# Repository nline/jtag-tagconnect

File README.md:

JTAG to Tag Connect
===================

This PCB is an adapter that converts the [20 pin JLink](https://www.segger.com/jlink-debug-probes.html) connector to
a [6-pin Tag Connect](http://www.tag-connect.com/TC2030-IDC-NL),
much like [this](https://www.segger.com/jlink-6-pin-adapter.html) board.
Ours, however, additionally contains an onboard LDO
that can supply 3.3V to the attached device and the VTRef pin on the J-Link programmer
so that it can program boards that are not self powered.

This most recent (nLine) version allows you to additionally power the target board with 5V and
also select the whether to keep the I/O at the supply voltage or divide it down from 5V to 3V3. 
This allows powering higher voltage boards while still operating the MCU at 3V3 without on-board
level shifters.

Interface
---------

- **Switch 1**, labeled `VSupply`: Set to 5V to connect teh VCC pin on the TagConnect
header (and the attached board) to the 5VC output from the JLink.
Set to `3V3` to connect the `VCC` pin on the TagConnect
header (and the attached board to be programmed) and the `VTRef` pin from
the Segger JLink to the 3.3 V output from the regulator.
Set to `DEV` to directly connect the `VTRef` pin on the JLink to the TagConnect
VCC pin. This sets the I/O voltage for the JLink, but does not power the target board.

- **Switch 2**, labeled `SWDIO`: This switch can connect the `SWDIO` and
`!RESET` signals, which is needed on some ICs. To leave the signals
disconnected, leave the switch in the empty (down) position.

- **Switch 3** labeled `VIO`: Set to `Supply` to use with I/O voltage same as VSupply. Set to
`5V->3V3` to divide a 5V supply down to 3V3 for 3V3 I/O operation.

Troubleshooting
---------------

1. Blue LED does not come on when attached to JLink.
You need to enable the 5 V output on the JLink:

        $ JlinkExe
        power on perm

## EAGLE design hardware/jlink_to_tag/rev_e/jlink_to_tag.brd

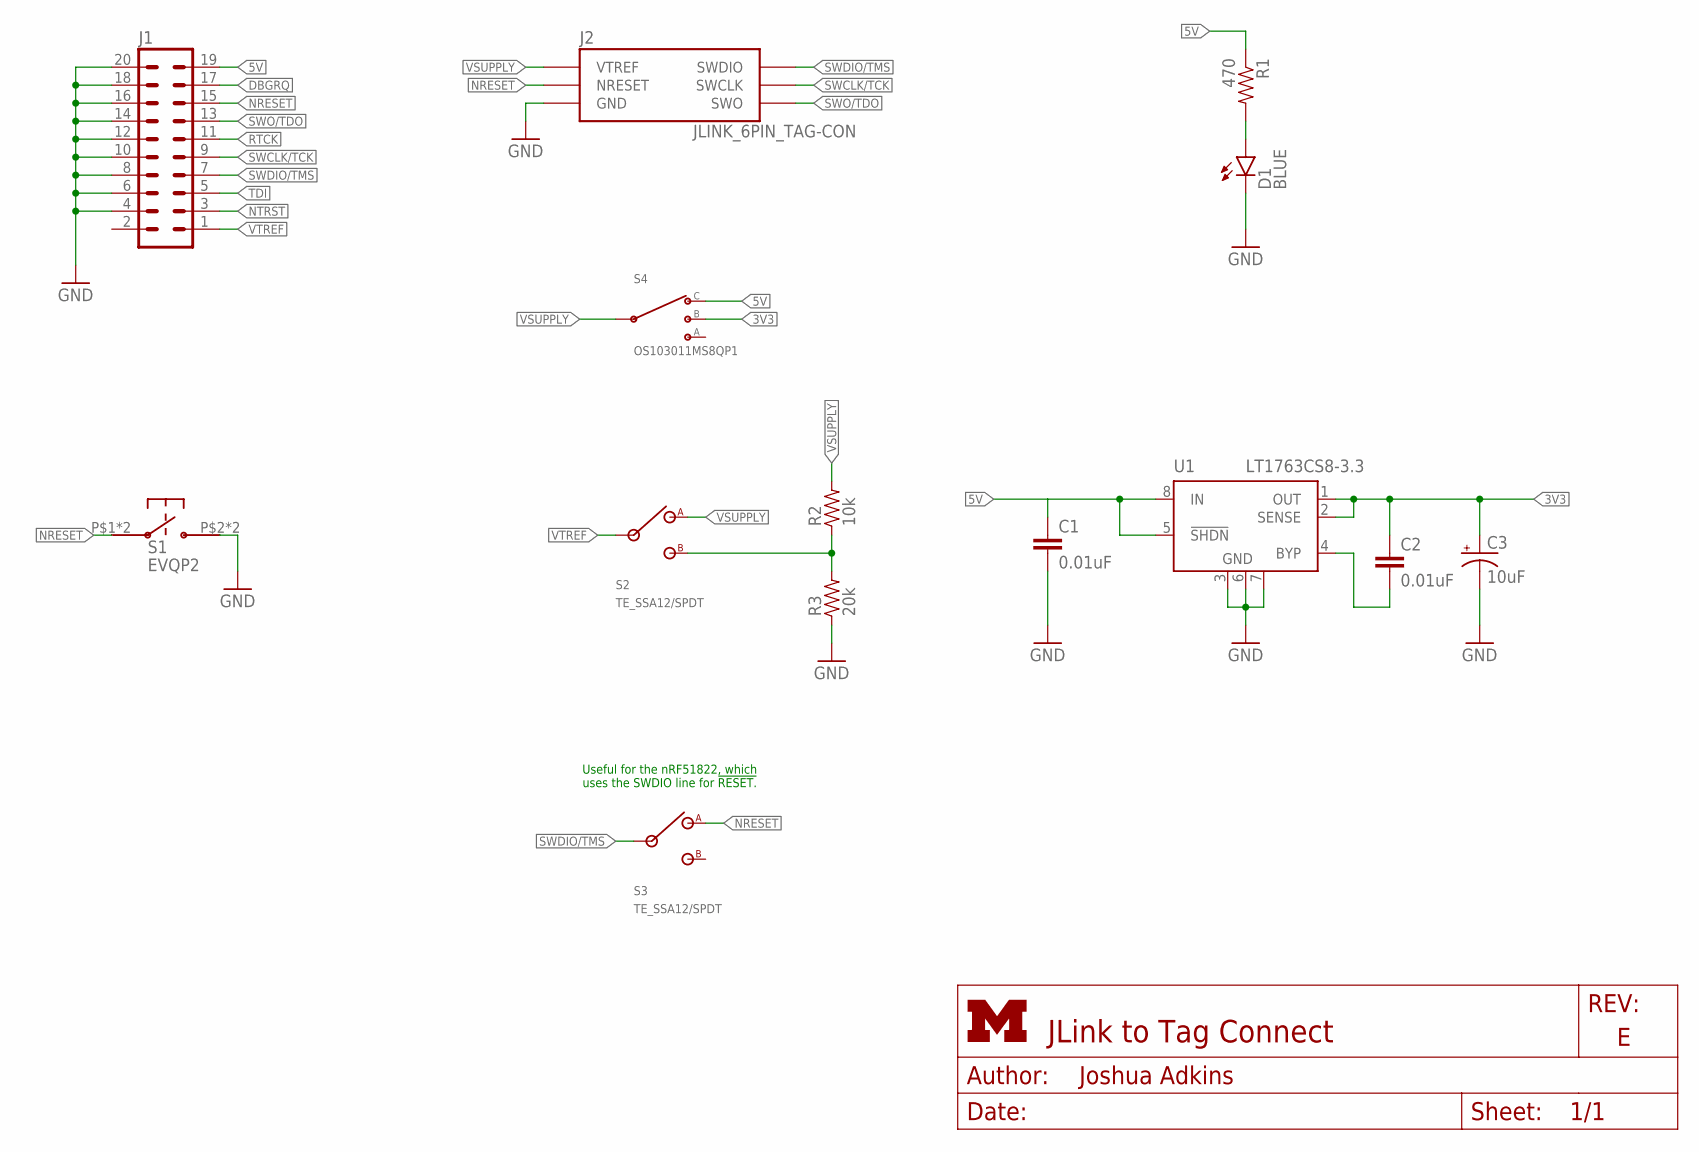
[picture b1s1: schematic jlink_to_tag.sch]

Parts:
C1, C2: 0.01uF; C0603; DIGIKEY 490-1512-1-ND
C3: 10uF; EIA3216; DIGIKEY 399-3684-1-ND
D1: BLUE; LED-0603; DIGIKEY 160-1827-1-ND
J1: ML20; DIGIKEY S9172-ND
J2: JLINK_6PIN_TAG-CON; 2X3_MALE_SHROUDED_0.100
R1: 470; 0603-RES; DIGIKEY P470DBCT-ND
R2: 10k; 0603-RES; DIGIKEY RMCF0603FT10K0CT-ND
R3: 20k; 0603-RES; DIGIKEY P20.0KHCT-ND
S1: EVQP2
S2, S3: TE_SSA12/SPDT; MPN SLW-883935-2A-D; DIGIKEY 2223-SLW-883935-2A-D-ND
S4: OS103011MS8QP1; OS102011MS8QP1
U1: LT1763CS8-3.3; SOIC8; DIGIKEY LT1763CS8-3.3#TRPBFCT-ND

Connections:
3V3: C2.1, C3.A (+), S4.3 (2), U1.1 (OUT), U1.2 (SENSE)
5V: C1.1, J1.19, R1.1, S4.4 (3), U1.5 (!SHDN), U1.8 (IN)
DBGRQ: J1.17
GND: C1.2, C3.C (-), D1.C, J1.4, J1.6, J1.8, J1.10, J1.12, J1.14, J1.16, J1.18, J1.20, J2.5 (GND), R3.1, S1.P$2, S1.P$4, U1.3 (GND), U1.6 (GND), U1.7 (GND)
unnamed: R2.1, R3.2, S2.2 (B)
unnamed: D1.A, R1.2
unnamed: C2.2, U1.4 (BYP)
NRESET: J1.15, J2.3 (NRESET), S1.P$1, S1.P$3, S3.1 (A)
NTRST: J1.3
RTCK: J1.11
SWCLK/TCK: J1.9, J2.4 (SWCLK)
SWDIO/TMS: J1.7, J2.2 (SWDIO), S3.IN
SWO/TDO: J1.13, J2.6 (SWO)
TDI: J1.5
VSUPPLY: J2.1 (VTREF), R2.2, S2.1 (A), S4.2 (C)
VTREF: J1.1, S2.IN

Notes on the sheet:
Useful for the nRF51822, which uses the SWDIO line for !RESET.

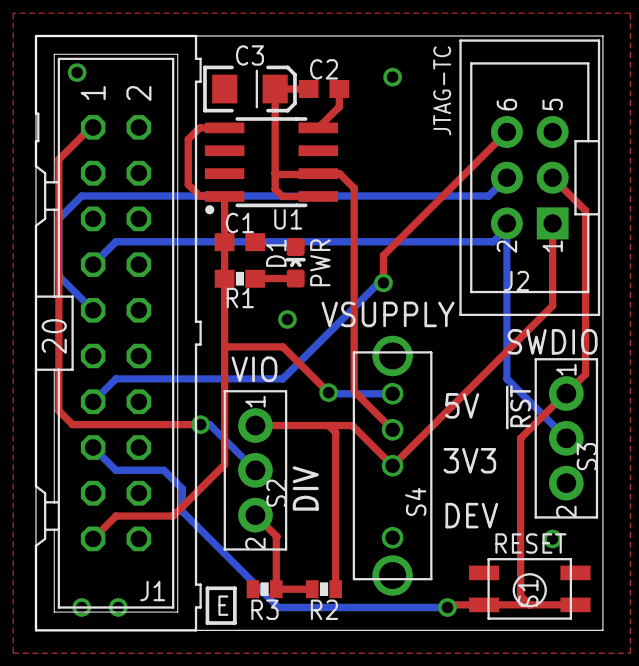
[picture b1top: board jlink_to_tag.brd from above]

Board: 2 copper layers, 31.5 x 33.0 mm, 14 parts (0 on the bottom side), 12 nets.

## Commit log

2024-01-17 add 3rd switch for 5V supply but 3V3 IO
2024-01-17 update part numbers
2024-01-17 add BOM and final changes

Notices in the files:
parts and their libraries:
SparkFun-Passives: Licensing: Creative Commons ShareAlike 4.0 International - https://creativecommons.org/licenses/by-sa/4.0
